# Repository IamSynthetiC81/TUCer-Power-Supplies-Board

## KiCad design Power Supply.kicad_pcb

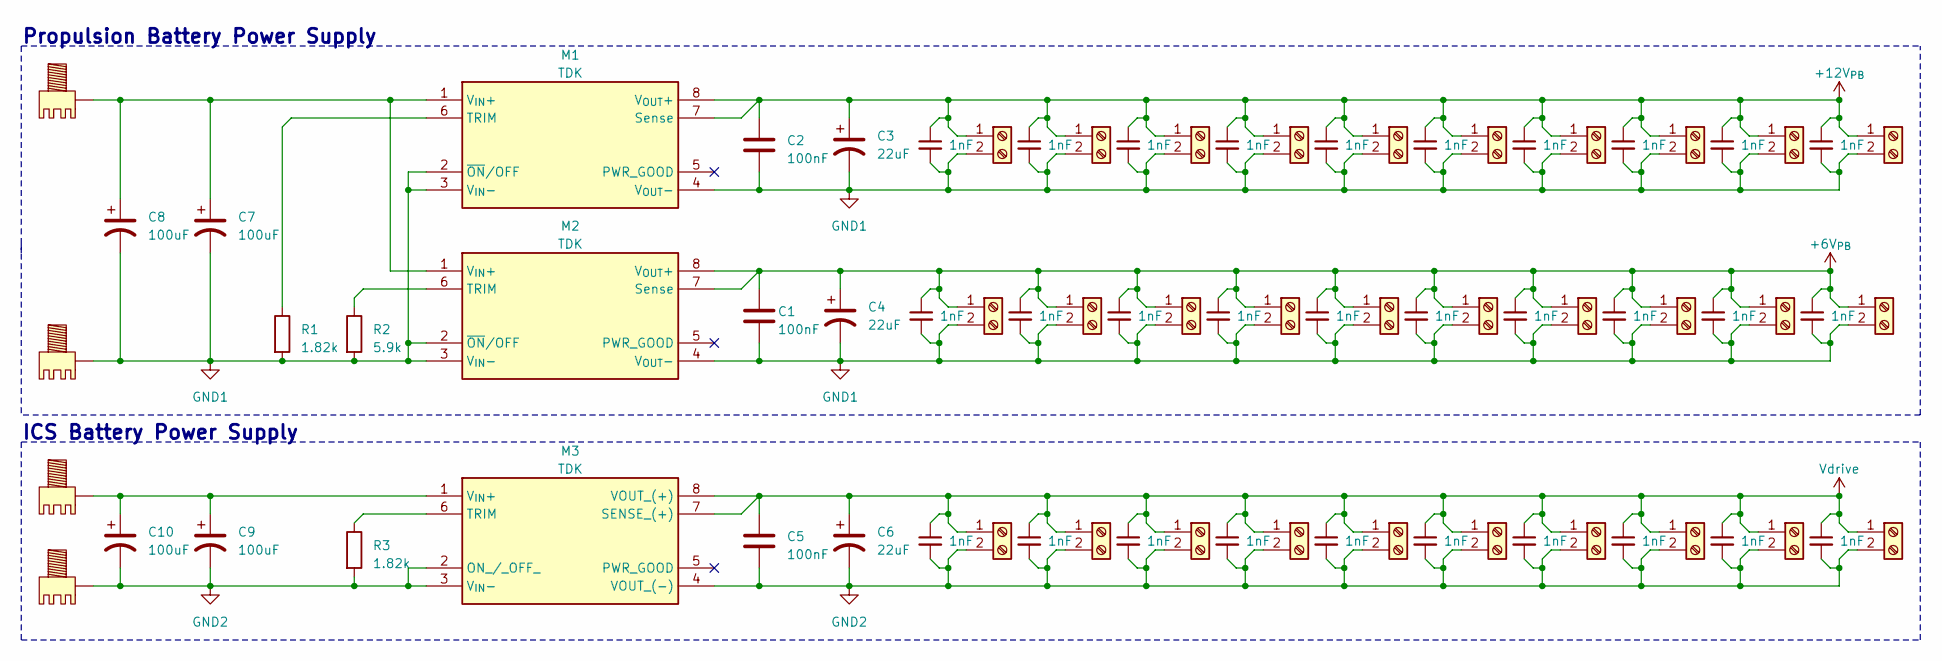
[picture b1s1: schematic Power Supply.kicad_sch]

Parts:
C1, C2, C5: 100nF; CP_Elec_4x5.8
C3, C4, C6: 22uF; CP_Elec_4x5.7
C7, C8, C9, C10: 100uF; CP_Radial_D8.0mm_P5.00mm
C11, C12, C13, C14, C15, C16, C17, C18, C19, C20, C21, C22, C23, C24, C25, C26, C27, C28, C29, C30, C31, C32, C33, C34, C35, C36, C37, C38, C39, C40: 1nF; C_Disc_D7.5mm_W5.0mm_P5.00mm
J1, J2, J21, J22: 7461383
J3, J4, J5, J6, J7, J8, J9, J10, J11, J12, J13, J14, J15, J16, J17, J18, J19, J20, J23, J24, J25, J26, J27, J28, J29, J30, J31, J32, J33, J34: Connector; JST_EH_B2B-EH-A_1x02_P2.50mm_Vertical
M1, M2, M3: TDK; I3A4W005A150V001R; Mouser Part Number 967-I3A4W005A150V01R
R1, R3: 1.82k; R_Axial_DIN0204_L3.6mm_D1.6mm_P7.62mm_Horizontal
R2: 5.9k; R_Axial_DIN0204_L3.6mm_D1.6mm_P7.62mm_Horizontal

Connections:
+6V: C1.1, C4.1, C21.1, C22.1, C23.1, C24.1, C25.1, C26.1, C27.1, C28.1, C29.1, C30.1, J9.1, J10.1, J11.1, J12.1, J13.1, J14.1, J27.1, J28.1, J29.1, J30.1, M2.7 (Sense), M2.8 (V_{OUT}+)
+12V: C2.1, C3.1, C11.1, C12.1, C13.1, C14.1, C15.1, C16.1, C17.1, C18.1, C19.1, C20.1, J3.1, J4.1, J5.1, J6.1, J7.1, J8.1, J23.1, J24.1, J25.1, J26.1, M1.7 (Sense), M1.8 (V_{OUT}+)
GND1: C1.2, C2.2, C3.2, C4.2, C7.2, C8.2, C11.2, C12.2, C13.2, C14.2, C15.2, C16.2, C17.2, C18.2, C19.2, C20.2, C21.2, C22.2, C23.2, C24.2, C25.2, C26.2, C27.2, C28.2, C29.2, C30.2, J2.1 (0), J3.2, J4.2, J5.2, J6.2, J7.2, J8.2, J9.2, J10.2, J11.2, J12.2, J13.2, J14.2, J23.2, J24.2, J25.2, J26.2, J27.2, J28.2, J29.2, J30.2, M1.2 (~ON/OFF), M1.3 (V_{IN}-), M1.4 (V_{OUT}-), M2.2 (~ON/OFF), M2.3 (V_{IN}-), M2.4 (V_{OUT}-), R1.2, R2.2
GND2: C5.2, C6.2, C9.2, C10.2, C31.2, C32.2, C33.2, C34.2, C35.2, C36.2, C37.2, C38.2, C39.2, C40.2, J15.2, J16.2, J17.2, J18.2, J19.2, J20.2, J22.1 (0), J31.2, J32.2, J33.2, J34.2, M3.2 (ON_/_OFF_), M3.3 (V_{IN}-), M3.4 (VOUT_(-)), R3.2
unnamed: C7.1, C8.1, J1.1 (0), M1.1 (V_{IN}+), M2.1 (V_{IN}+)
unnamed: C9.1, C10.1, J21.1 (0), M3.1 (V_{IN}+)
unnamed: M1.6 (TRIM), R1.1
unnamed: M2.6 (TRIM), R2.1
unnamed: M3.6 (TRIM), R3.1
Vdrive: C5.1, C6.1, C31.1, C32.1, C33.1, C34.1, C35.1, C36.1, C37.1, C38.1, C39.1, C40.1, J15.1, J16.1, J17.1, J18.1, J19.1, J20.1, J31.1, J32.1, J33.1, J34.1, M3.7 (SENSE_(+)), M3.8 (VOUT_(+))

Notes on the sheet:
Propulsion Battery Power Supply
ICS Battery Power Supply

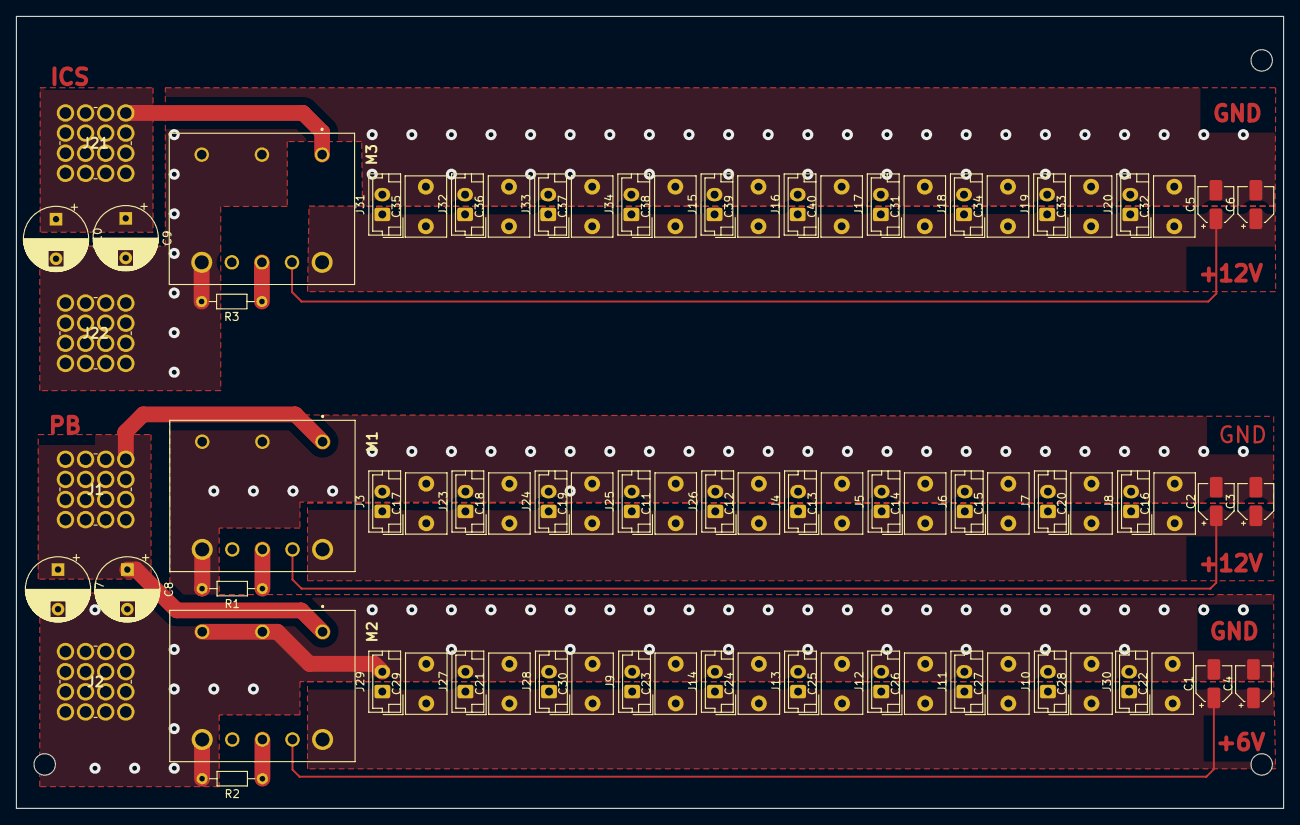
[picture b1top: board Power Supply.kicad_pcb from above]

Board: 2 copper layers, 160.0 x 100.0 mm, 83 parts (0 on the bottom side), 10 nets.

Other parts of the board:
MH2, MH3, MH4: MountingHole_2.7mm_M2.5_DIN965

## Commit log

2023-05-16 Added Datasheets
2023-05-17 Power Supplie Board V1.00
